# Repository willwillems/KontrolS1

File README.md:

The following info is all about the S4 MK1, the MK2 has a different (non-panelized) PCB design and thus doesn't allow for reusing the original PCB's without serious modifications. The MK3 also has a single PCB for the mixer and deck sections.

## Setup
- Use the `Kontrol_S1_LC_OLED` sketch
- Either `#include "unit_d.h"` or `#include "unit_c.h"` based on the unit
- Uncomment `#define SCREEN` if using the OLED module
- Edit the `MIDI_NAME` in the `name.c` file to the desired name (these cannot conflict with other S1 units you're using)
- Flash the firmware

## Led off states
All leds are controlled by a transistor activated by the 595 chip. However not all are connected the same way, sending 6 all-off byte packages (`0b00000000`) will turn some of the LED's on, these specific bits to be set to HIGH instead of LOW in order to be turned off.

```
// LED OFF STATES from least significant bit (so notation is in reverse)
// -- BYTE [0]: 0b01010101 --
// CUE1 green - CUE1 blue - CUE2 green - CUE2 blue - CUE3 green - CUE3 blue - CUE4 green - CUE4 blue 
// -- BYTE [1]: 0b00000000 --
// Sample 1 - Sample 2 - Sample 3 - Sample 4 - SYNC - CUE - PLAY - SHIFT
// -- BYTE [2]: 0b11000000 --
// ON AIR - SAMPLES - DECK A/B - DECK C/D - KEYLOCK - MASTER - TEMPO OFFSET UP - TEMPO OFFSET DOWN
// -- BYTE [3]: 0b00000000 --
// LOOP IN - LOOP OUT - TOGGLE DECK C/D - LOAD - NONE - NONE - NONE -NONE
// -- BYTE [4]: 0b11111111 -- LEFT DIGIT
// UP-MIDDLE - UP-RIGHT - DOT - UP-LEFT - DOWN-LEFT - DOWN-MIDDLE - MIDDLE-MIDDLE - DOWN-RIGHT
// -- BYTE [5]: 0b11111111 -- RIGHT DIGIT
// DM - DL - UL - UM - UR - DR - MM - DOT
```

## Button off states
The first four bits of the last packet are connected to GND trough some 330 R resistors. 

```
// BUTTON OFF STATES
// -- BYTE [0]: 0B00000000 --
// PLAY - CP4 - CUE - CP3 - SYNC - CP2 - SHIFT - CP1
// -- BYTE [1]: 0B00000000 --
// S4 - LOAD - S3 - LOOP OUT - S2 - LOOP IN - DECK C/D
// -- BYTE [2]: 0B00001100 --
// X - X - X - X - ENC-R BUT - ENC-L BUT - OFFSET DOWN - OFFSET UP
```

## Pinout
This is the pinout for the DECK A board the DECK B connector is almost identical (but mirrored). The two exceptions are pin 2 and 13, ~~I have no idea what pin 2 is~~ pin 2 is the 165's DS on the DECK B unit. Click [here](https://i.imgur.com/EdCKgI3.jpg) for the DECK B section.

> WARNING: Pinout changed, check below.

```
// 595’s output enable is connected to GND.
// 165’s CE (chip enable) is connected to GND.
// (13, 14, 15), (16, 17) and (18, 19) are connected together.

1. Q7 (serial out 165)
2. GND (DS from 165's on DECK B)
3. PL (latch pin 165)
4. CP (clock input 165)
5. ENC4-R (330 R)
6. ENC5-L (330 R)
7. ENC4-R (330 R)
8. ENC5-L (330 R)
9. Q7S (serial out 595) (for DECK B this is the serial out of the 4 upper 595's)
10. DS (serial in 595) (for DECK B this is the serial in of the 2 lower 595's)

11. ST_CP (latch pin 595)
12. SH_CP (clock input 595)
13. GND (For DECK B this is the serial in for the 4 upper 595's)
14. GND
15. GND
16. LED V1 (5v but can just be 3.v)
17. LED V1 (5v but can just be 3.v)
18. LED V2 (3.3v)
19. LED V2 (3.3v)
20. VCC

1. GND
2. VCC
3. POT
4. GND
```

## Chip connections

### 74HC595

There are 6 595 chips chained together (the serial out(`Q7S`) for the last 595 is exposed as pin 9 on the connector).

- `ST_CP` and `SH_CP` of every chip are connected to connector pin 11 and 12.
- `MR` is connected to `VCC` on every chip.
- Output enable (`OE`) is connected to `GND` on every chip.

### 74HC165

There are 3 165 chips chained together.

- Clock enable(`CE`) is connect to `GND` on every chip.
- `PL` and `CP` of every chip are connected to connector pin 3 and 4.

## Jog wheels

The rotation of the jogs is measured by two photo-interrupters ([KTIR0611S](http://www.farnell.com/datasheets/2307823.pdf)). The "push down" of the jog is measured by a photo sensor that gets blocked when you push the platter down on it.

### Connections
The 6 pin JST connector is connected to the circuit with the two photo-interrupters. There is also a connection to a third photo-interrupter but they did not end up mounting and integrating this third one into the final product.
```
1. VCC (3.3v)
2. VCC (3.3v) (this "enables" the optical readings?) 
3. GND
4. ENC R
5. ENC L
6. ENC M (not connected or mounted)
```
The 3 color push cable coming out of the jog:
```
BLUE. GND
RED. VCC (3.3V)
WHITE. SIGNAL (analog read: 800~900 off, 1023 on)
-. DUMMY (unused pin on 4-pin JST connector) 
```
> ## Warning
> The jog press is not yet working so the info about it is possibly wrong. The MK1 does seem to use a IR proximity sensor (probably the [HSDL-9100-024](https://docs.broadcom.com/doc/AV02-2259EN) but so far no reliable readings have been produced. The MK2 uses an Ambient Light Sensor with an I2C Interface called the [VNCL4000](https://cdn-shop.adafruit.com/datasheets/vcnl4000.pdf). The current MK1 problems might just be calibration issues but could also be something more serious.

## Observations
- VCC should be 3.3v, not 5v. The 595 works with 5v and you will not fry the LED's but the 165 will not work and you might damage it.
- You can easily run the 165 and 595 chips with hardware SPI.
- The left and right circuit board are not identical at all though the connectors appear to be.

## Custom FX PCB

The custom FX PCB has the same layout on both sides so only one version is required (it has both the L&R mounting holes). The custom FX PCB provides a 165 and 595 interface for the buttons and LED's respectively and a separate connector for the potentiometer signals.

### Pinout

```
1. INH (165-15) [Clock enable]
2. SER (165-10) [Serial data input]
3. QH (595-9) [Serial data output]
4. LATCH 165 (165-1) [Parallel load input]
5. RCK (595-12) [storage register clock input]
6. QH (165-9) [Serial out]
7. SER (595-14)[Serial data input]
8. CLOCK
9. GND
10. VCC

11. VCC
12. GND
13. FX_3
14. FX_2
15. FX_1
16. FX_DW
```

## Parts

These simplified BOM's are for the MK4 releases of the brain and pot boards.

### Brain board

These are the parts needed to populate 1 brain board, to convert one S4 to two S1 units you'd need these parts x2.

| Part                                   | Amount | Value |
| -------------------------------------- | ------ | ----- |
| Molex Picoblade (1.25mm) 10-pin        | 3      |       |
| Molex Picoblade (1.25mm) 8-pin         | 1      |       |
| Molex Picoblade (1.25mm) 6-pin         | 3      |       |
| Molex Picoblade (1.25mm) 4-pin         | 2      |       |
| M3 metal standoffs                     | 4      | 15mm  |
| M3 metal screws                        | 8      | 6mm   |
| USB-B socket                           | 1      |       |
| Teensy LC                              | 1      |       |
| Capacitor US 1206                      | 1      | 100nF |
| Resistor US 1206 (0805 compatible)     | 1      | 1M    |

The 1M resistor might need a higher value.

### Pot board

These are the parts needed to populate 1 brain board, to convert one S4 to two S1 units you'd need these parts x2. The standoffs needed are already included with the brain BOM.

| Part                                   | Amount | Value |
| -------------------------------------- | ------ | ----- |
| Molex Picoblade (1.25mm) 10-pin        | 1      |       |
| Molex Picoblade (1.25mm) 6-pin         | 1      |       |
| Resistor US 0805                       | 5      | 82    |
| Resistor US 0805                       | 8      | 10K   |
| 74HC595D                               | 1      |       |
| 74HC165D                               | 1      |       |
| Capacitor US 1206                      | 6      | 100nF |

The four capacitors for the potentiometers might need a lower value.

## Custom OLED PCB

Contains adapter from 1.25mm JST to OLED, a step-up to 12V and some passive components the OLED driver needs.

### Pinout

```
1. GND
2. CLOCK
3. GND
4. MOSI
5. SS-SCREEN
6. VCC
7. DC
8. RST
```

# Screen

The screen uses https://github.com/ErikMinekus/traktor-api-client to get data from traktor + a local server to send it to the teensy over serial.

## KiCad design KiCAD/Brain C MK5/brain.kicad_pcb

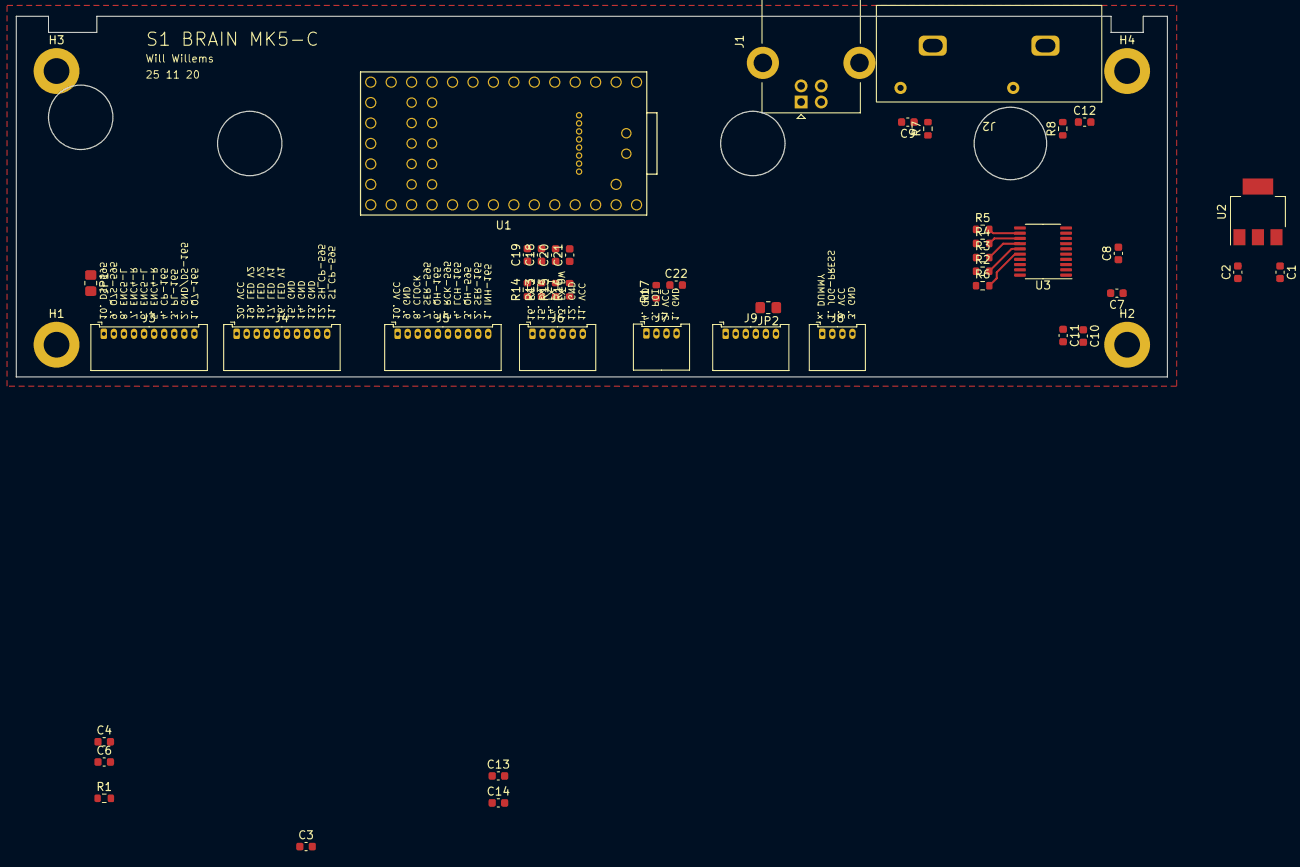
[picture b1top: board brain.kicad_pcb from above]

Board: 4 copper layers, 143.0 x 44.8 mm, 49 parts (0 on the bottom side), 49 nets.

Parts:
C1, C3, C4, C6, C10: 100nF; C_0603_1608Metric
C2, C11: 10uF; C_0603_1608Metric
C7, C8: 2.2uF; C_0603_1608Metric
C9, C12: 2.2nF; C_0603_1608Metric
C13, C14: C_Small; C_0603_1608Metric
C18, C19, C20, C21, C22: 1.2uF; C_0603_1608Metric
H1, H2, H3, H4: MountingHole_Pad; MountingHole_3.2mm_M3_ISO7380_Pad
J1: USB_B; USB_B_Lumberg_2411_02_Horizontal
J2: Conn_Coaxial_x2_Isolated; RCA_double
J3, J4, J5: Conn_01x10; Molex_PicoBlade_53048-1010_1x10_P1.25mm_Horizontal
J6, J9: Conn_01x06; Molex_PicoBlade_53048-0610_1x06_P1.25mm_Horizontal
J7, J8: Conn_01x04; Molex_PicoBlade_53048-0410_1x04_P1.25mm_Horizontal
JP1, JP2: Jumper_2_Bridged; R_0805_2012Metric_Pad1.20x1.40mm_HandSolder
R1: 10R; R_0603_1608Metric
R2, R3, R4, R5: 22; R_0603_1608Metric
R6: 0; R_0603_1608Metric
R7, R8: 470; R_0603_1608Metric
R13, R14, R15, R16, R17: 2.2K; R_0603_1608Metric
U1: Teensy4.0; Teensy40_SMT
U2: LD1117S33TR_SOT223; SOT-223-3_TabPin2
U3: PCM5102; TSSOP-20_4.4x6.5mm_P0.65mm

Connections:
+3.3V: C4.1, C6.1, U1.16 (3V3), U1.31 (3V3), U3.1 (CPVDD), U3.20 (DVDD)
+3.3VA: C2.1, C10.1, C11.1, U2.2 (VO), U3.8 (AVDD), U3.17 (XSMT)
+5V: C14.1, R1.1
/165-LATCH: J3.8, J5.7, U1.11 (9_OUT1C)
/595-LATCH: J4.10, J5.6, U1.10 (8_TX2_IN1)
/CE-595-165: J3.9, J5.10, U1.12 (10_CS_MQSR)
/CLOCK: J3.7, J4.9, J5.3, U1.20 (13_SCK_CRX1_LED)
/Connectors/165_BRIDGE: J3.10, J5.9
/Connectors/595_BRIDGE: J3.1, J5.8
/Connectors/595_OUT_MAIN: J3.2, JP1.2 (B)
/DAC (PCM5102)/AUDIO_OUT_L: C12.1, R8.2
/DAC (PCM5102)/AUDIO_OUT_R: C9.1, R7.2
/DAC (PCM5102)/LDO: C3.1, U3.18 (LDOO)
/ENCL1: J3.5, U1.4 (2_OUT2)
/ENCL2: J3.6, U1.5 (3_LRCLK2)
/ENCR1: J3.3, U1.6 (4_BCLK2)
/ENCR2: J3.4, U1.7 (5_IN2)
/FADER_1: J7.2, R17.1
/JOG-MOVE1: J9.2, U1.8 (6_OUT1D)
/JOG-MOVE2: J9.3, U1.9 (7_RX2_OUT1A)
/JOG_PRESS_IR: J8.2, U1.21 (14_A0_TX3_SPDIF_OUT)
/MISO: J5.5, U1.14 (12_MISO_MQSL)
/MOSI: J5.4, U1.13 (11_MOSI_CTX1)
/POT_1: J6.1, R14.1
/POT_2: J6.2, R13.1
/POT_3: J6.3, R15.1
/POT_4: J6.4, R16.1
/USB_D+: J1.3 (D+), U1.54 (D+)
/USB_D-: J1.2 (D-), U1.53 (D-)
GND: C1.2, C2.2, C3.2, C4.2, C6.2, C8.2, C9.2, C10.2, C11.2, C12.2, C13.2, C14.2, C18.2, C19.2, C20.2, C21.2, C22.2, H1.1, H2.1, H3.1, H4.1, J1.4 (GND), J1.5 (Shield), J2.2 (Ext1), J2.4 (Ext2), J4.6, J4.7, J4.8, J5.2, J6.5, J7.1, J7.4, J8.4, J9.4, JP1.1 (A), R6.1, U1.1 (GND), U1.17 (GND), U1.32 (GND), U2.1 (GND), U3.3 (CPGND), U3.9 (AGND), U3.10 (DEMP), U3.11 (FLT), U3.19 (DGND)
unnamed: J9.5, JP2.2 (B)
unnamed: C19.1, R14.2, U1.22 (15_A1_RX3_SPDIF_IN)
unnamed: C18.1, R13.2, U1.23 (16_A2_RX4_SCL1)
unnamed: C20.1, R15.2, U1.24 (17_A3_TX4_SDA1)
unnamed: C21.1, R16.2, U1.25 (18_A4_SDA0)
unnamed: C22.1, R17.2, U1.26 (19_A5_SCL0)
unnamed: C1.1, R1.2, U2.3 (VI)
unnamed: R4.2, U3.13 (BCK)
unnamed: C7.2, U3.4 (CAPM)
unnamed: C7.1, U3.2 (CAPP)
unnamed: R3.2, U3.14 (DIN)
unnamed: R6.2, U3.16 (FMT)
unnamed: R2.2, U3.15 (LRCK)
unnamed: R8.1, U3.6 (OUTL)
unnamed: R7.1, U3.7 (OUTR)
unnamed: R5.2, U3.12 (SCK)
unnamed: C8.1, U3.5 (VNEG)
VBUS: C13.1, J1.1 (VBUS), U1.33 (VIN), U1.34 (VUSB)
VCC: J4.1, J4.2, J4.3, J4.4, J4.5, J5.1, J6.6, J7.3, J8.3, J9.6, JP2.1 (A)

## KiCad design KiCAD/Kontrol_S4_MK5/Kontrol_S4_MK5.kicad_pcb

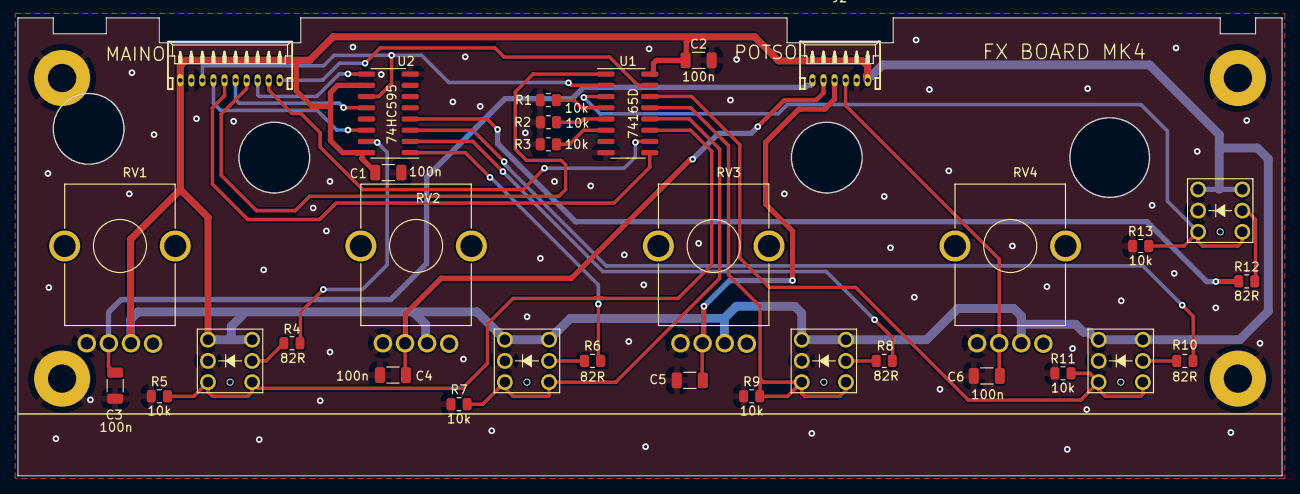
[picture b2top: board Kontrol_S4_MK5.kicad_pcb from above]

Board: 2 copper layers, 143.0 x 51.8 mm, 36 parts (0 on the bottom side), 32 nets.

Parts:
C1, C2, C3, C4, C5, C6: 100n; C_1206_3216Metric
H1, H2, H3, H4: STANDOFF_ELECTRICAL; STANDOFF-ELECTRICAL
J1: Conn_01x10; CON_MAINO
J2: Conn_01x06; CON_POTSO
R1, R2, R3, R5, R7, R9, R11, R13: 10k; R_0805_2012Metric
R4, R6, R8, R10, R12: 82R; R_0805_2012Metric
RV1: FX_DWO; Potentiometer_custom
RV2: FX_1; Potentiometer_custom
RV3: FX_2; Potentiometer_custom
RV4: FX_3; Potentiometer_custom
SW1, SW2, SW3, SW4, SW5: Button; BUTTON
U1: 74165D; SOIC-16_3.9x9.9mm_P1.27mm
U2: 74HC595; SOIC-16_3.9x9.9mm_P1.27mm

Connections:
/165_IN: J1.2, U1.10 (SER)
/595_OUT: J1.3, U2.9 (QH')
/A1: C3.1, J2.6, RV1.2
/A2: C4.1, J2.5, RV2.2
/A3: C5.1, J2.4, RV3.2
/A4: C6.1, J2.3, RV4.2
/CE_165: J1.1, U1.15 (CLK_INH)
/CLOCK: J1.8, U1.2 (CLK), U2.11 (SRCLK)
/D1: R5.2, SW1.1, U1.11 (A)
/D2: R7.2, SW2.1, U1.12 (B)
/D3: R9.2, SW3.1, U1.13 (C)
/D4: R11.2, SW4.1, U1.14 (D)
/D5: R13.2, SW5.1, U1.3 (E)
/D6: R1.2, U1.4 (F)
/D7: R2.2, U1.5 (G)
/D8: R3.2, U1.6 (H)
/LATCH_165: J1.4, U1.1 (SH/LD)
/LATCH_595: J1.5, U2.12 (RCLK)
/MISO: J1.6, U1.9 (QH)
/MOSI: J1.7, U2.14 (SER)
GND: C1.2, C2.2, C3.2, C4.2, C5.2, C6.2, H1.P1, H2.P1, H3.P1, H4.P1, J1.9, J2.2, R1.1, R2.1, R3.1, R5.1, R7.1, R9.1, R11.1, R13.1, RV1.3, RV2.3, RV3.3, RV4.3, SW1.LED-, SW2.LED-, SW3.LED-, SW4.LED-, SW5.LED-, U1.8 (GND), U2.8 (GND)
unnamed: R4.1, U2.15 (QA)
unnamed: R4.2, SW1.LED+
unnamed: R6.1, U2.1 (QB)
unnamed: R6.2, SW2.LED+
unnamed: R8.1, U2.2 (QC)
unnamed: R8.2, SW3.LED+
unnamed: R10.1, U2.3 (QD)
unnamed: R10.2, SW4.LED+
unnamed: R12.1, U2.4 (QE)
unnamed: R12.2, SW5.LED+
VCC: C1.1, C2.1, J1.10, J2.1, RV1.1, RV2.1, RV3.1, RV4.1, SW1.2, SW2.2, SW3.2, SW4.2, SW5.2, U1.16 (VCC), U2.10 (~SRCLR), U2.16 (VCC)

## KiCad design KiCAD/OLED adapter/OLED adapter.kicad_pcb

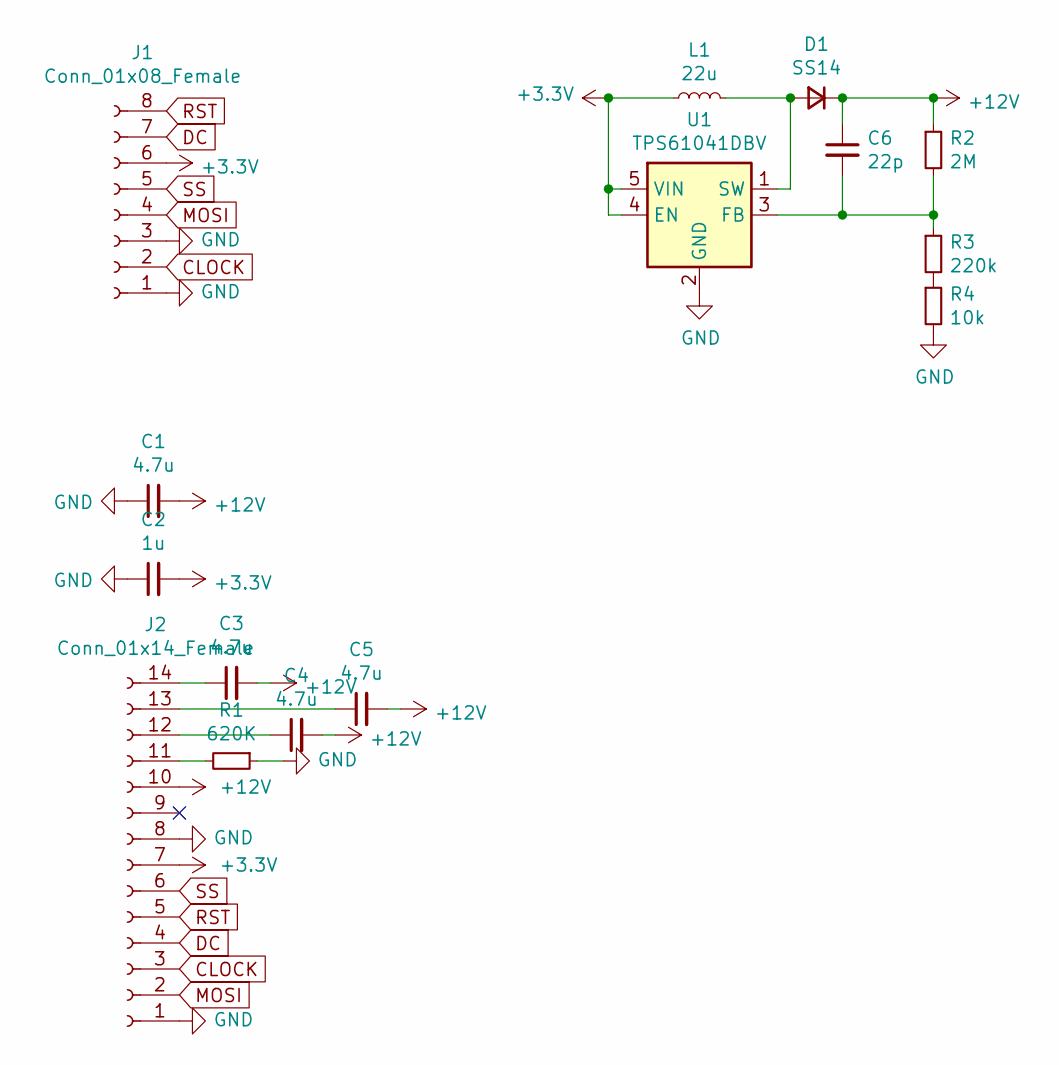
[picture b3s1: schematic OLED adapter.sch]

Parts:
C1, C3, C4, C5: 4.7u; C_0603_1608Metric_Pad1.05x0.95mm_HandSolder
C2: 1u; C_0603_1608Metric_Pad1.05x0.95mm_HandSolder
C6: 22p; C_0603_1608Metric_Pad1.05x0.95mm_HandSolder
D1: SS14; D_SMA_Handsoldering
J1: Conn_01x08_Female; Hirose_DF13-08P-1.25DS_1x08_P1.25mm_Horizontal
J2: Conn_01x14_Female; TE_1-1734839-4_1x14-1MP_P0.5mm_Horizontal
L1: 22u; L_0805_2012Metric_Pad1.15x1.40mm_HandSolder
R1: 620K; R_0603_1608Metric_Pad1.05x0.95mm_HandSolder
R2: 2M; R_0603_1608Metric_Pad1.05x0.95mm_HandSolder
R3: 220k; R_0603_1608Metric_Pad1.05x0.95mm_HandSolder
R4: 10k; R_0603_1608Metric_Pad1.05x0.95mm_HandSolder
U1: TPS61041DBV; SOT-23-5_HandSoldering

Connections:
+3V3: C2.2, J1.6, J2.7, L1.1, U1.4 (EN), U1.5 (VIN)
+12V: C1.2, C3.2, C4.2, C5.2, C6.1, D1.1 (K), J2.10, R2.1
CLOCK: J1.2, J2.3
DC: J1.7, J2.4
GND: C1.1, C2.1, J1.1, J1.3, J2.1, J2.8, R1.1, R4.2, U1.2 (GND)
MOSI: J1.4, J2.2
unnamed: C3.1, J2.14
unnamed: C4.1, J2.12
unnamed: C5.1, J2.13
unnamed: C6.2, R2.2, R3.1, U1.3 (FB)
unnamed: D1.2 (A), L1.2, U1.1 (SW)
unnamed: J2.11, R1.2
unnamed: R3.2, R4.1
RST: J1.8, J2.5
SS: J1.5, J2.6

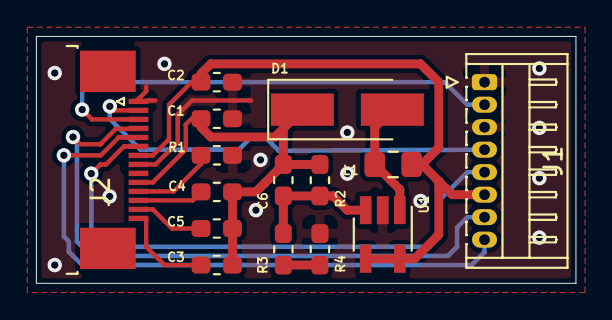
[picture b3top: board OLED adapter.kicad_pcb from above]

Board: 2 copper layers, 30.0 x 13.7 mm, 15 parts (0 on the bottom side), 15 nets.

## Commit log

2020-01-24 working encoders, leds and display
2020-01-27 Add comments, write untested 165 read, fix vars
    - Add some comments to clarify functionality.
    - Fix some var names.
    - Add logging of 74HC165 input states on LED read, does not work yet.
2020-01-28 Create README
    Add chip info, pinout and default LED state.
2020-01-29 add jog section
2020-01-30 add working button reading
2020-01-30 Add jog pinouts, button packages/mapping & observations
2020-02-12 Add info about MK2 PCB
2020-02-12 add info about MK3 PCB
2020-05-08 Upload display demo
2020-05-09 Fully working demo
2020-05-09 Client for demo
2020-05-12 Add info about right DS pin to pinout
2020-05-12 Figure out jogs
2020-05-12 Fix potentiometer pinout
2020-05-12 Add pic from other PCB
2020-05-13 Change SPI speed, add jog & fader support
2020-05-13 Fix 165's not working
2020-05-16 Add early CAD files
2020-05-16 Add custom PCB pinout
2020-05-17 Add general description of FX PCB and about pinout
2020-05-19 Design logo
2020-05-19 Add header
2020-05-19 Fix logo alignment
2020-05-25 Add MK1 gerbers of boards to repo
2020-06-18 Add FX board integration, invert tempo & right encoder, fix 1 typo
2020-06-18 Add gerbers second revision FX board
2020-06-23 clean up project structure
2020-06-23 add info about 4 pin jog touch connector
2020-07-02 add warning posssible wrong info jog press working
2020-07-02 Update jog press warning
2020-09-22 add new gen board designs
2020-10-03 Add OLED PCB connections
2020-10-04 Add custom OLED board
2020-10-07 add note about 595 serial flow extra pin
2020-10-07 Substitute confusing left-right refrences for A-B
2020-10-17 add traktor mapping for S1-R
2020-10-17 add code for new brain
2020-10-19 update mapping
2020-10-19 Add draft of MK3 board
2020-10-19 extend ledmap for sample and range buttons
2020-10-25 D unit working, add buttonmap, multideck structure
2020-11-02 Add correct OLED driver pinout
2020-11-10 Quick screen update
2020-11-25 Add MK4 designs
2020-11-25 add FX board MK4
2020-11-25 add newest OLED LC sketch
2020-11-28 Fix small bugs add cue 5-8 fix loop-move bug
2020-11-28 add better debouncing and generalise
2020-12-09 Add simple BOM's
2020-12-09 add standoff length
2021-09-20 add screws to BOM
2021-10-27 fuck...
2021-10-27 update screw length
2021-10-27 remove outdated info
2021-10-27 update silkscreen
2021-10-31 update file
2021-10-31 update sketch
2022-10-16 c changes
2023-03-18 add 3d files for body smoothing
2023-03-18 start eagle conversion to KiCAD
2023-03-18 implement more reliable jog readings
2023-06-25 add info photo sensor
2023-07-04 add nect-gen KiCAD files
2023-07-09 add jog press schematic
2023-07-09 work
